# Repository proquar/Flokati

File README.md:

Flokati
=======

Flokati is a collaborative ad-hoc automation system consisting of a
(relatively) low-speed rf-part based on AVR-microcontrollers and Nordic's
NRF-ICs, an OpenWrt-based WiFi-Gateway and an Android-App as a frontend.

For convenience the Android-App and OpenWrt-package for ar71xx are provided
in binary too.

History / Motivation / Overview
===============================

The original idea was to build a system of battery-powered devices for off-
the-grid outdoor parties, it should be:
* absolutely easy to set up and to use
* fast and responsive
* used simultaneously by a few people (and be robust at that)
* relatively cheap to build

Overall it already works very well, it still has some shortcomings, but I am
working on those.

Flokati-Parts
-------------

**Devices**

*	Currently there are only some spotlights and a mirror ball motor that I
	built around the Atmega88 and NRF24L01+.
	Devices have a unique 64bit address and can have multiple controllable
	elements (e.g. brightness, speed).
	Devices use Nordic's proprietary 2.4GHz NRF-technology (which was chosen
	because it is really cheap, much cheaper than e.g. 802.15.4).

**Gateway**

*	There needs to be a bridge between the IP-world and the proprietary
	rf-world. Here it is an OpenWrt-based WiFi access point (a battery powered
	TP-Link MR11U in my case) that also acts as a DCHP-server and hosts the
	device database.

**Frontend**

*	At the moment there's only the Android-App, which discovers new devices,
	requests device metadata from the device database and allows low-level
	control of discovered devices.

Architecture
------------

On the IP-side Flokati makes heavy use of IP-multicast. The bridge and the
Android devices all join a multicast group, and changes on one Android device
are immediately visible on the others. All actions on either side (NRF and IP)
are as fast as possible broadcast to the other side.

Controllable devices broadcast notify-messages with their ID and current
settings regularly, which are received by the frontend. The frontend then looks
up metadata (like name and controllable sinks) for that device from a database
which is also distributed in a multicast group. (Though the database currently
runs on the OpenWrt gateway and is not yet distributed)

So it is also possible to have controllable devices on the IP-side, so there
are currently no implementations for this. I will also add a mechanism for
remote configuration of some devices in the near future.

Directories
===========

**/avr**

*	These are some small devices I have built, there's a spotlight, which is
	able to PWM-dim or strobe a led. A mirror ball motor with controllable
	speed and direction. And the serial<->NRF gateway that is attached to the
	OpenWrt router.
	I will add hardware schematics and board layouts later.

**/Flokati-android**

*	This is the Android App as an Eclipse project. It's tiny and without any
	additional libraries. 

**/json-db**

*	Device metadata currently used by the database server on the OpenWrt
	router. Temporary solution. Should be put into /etc/flokati/db.

**/linux/flokati**

*	This is the OpenWrt package, consisting of two server-executables (bridge
	and database) and an init-script. The bridge can indicate it's status with
	a LED, that can be configured in the init-script.

**/flokati/python**

*	A few python tools, that I used during development. They do the same as the
	C-servers for OpenWrt.

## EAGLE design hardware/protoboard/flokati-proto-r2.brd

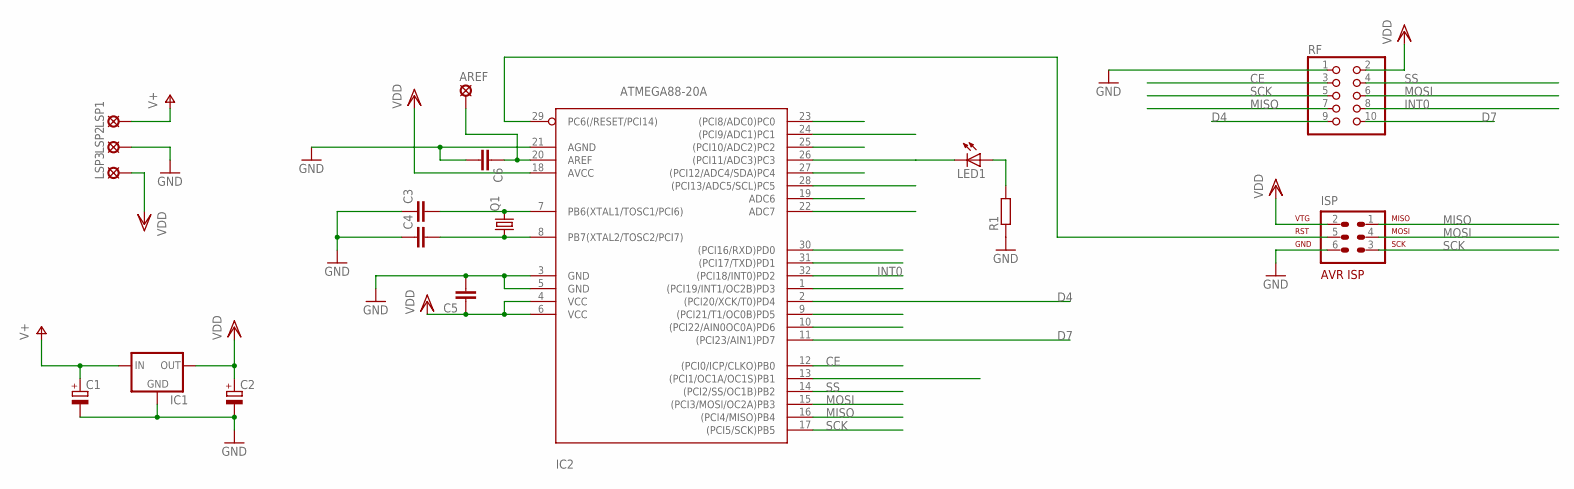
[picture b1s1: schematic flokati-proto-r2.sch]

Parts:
AREF: LSP10
C1, C2: CPOL-EUE2-4; E2-4
C3, C4, C5, C6: C-EUC0805K; C0805K
IC1: 78XXS
IC2: ATMEGA88-20A; TQFP32-08
ISP: AVR-ISP-6
LED1: LEDCHIP-LED0805; CHIP-LED0805
LSP1, LSP2, LSP3: LSP11
Q1: CRYSTALHC49U70; HC49U70
R1: R-EU_M0805; M0805
RF: PINHD-2X5; 2X05

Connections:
CE: IC2.12 ((PCI0/ICP/CLKO)PB0), RF.3
D4: IC2.2 ((PCI20/XCK/T0)PD4), RF.9
D7: IC2.11 ((PCI23/AIN1)PD7), RF.10
GND: C1.-, C2.-, C3.1, C4.1, C5.2, C6.2, IC1.GND, IC2.3 (GND), IC2.5 (GND), IC2.21 (AGND), ISP.6, LSP2.MP, R1.1, RF.1
INT0: IC2.32 ((PCI18/INT0)PD2), RF.8
MISO: IC2.16 ((PCI4/MISO)PB4), ISP.1, RF.7
MOSI: IC2.15 ((PCI3/MOSI/OC2A)PB3), ISP.4, RF.6
unnamed: C3.2, IC2.7 (PB6(XTAL1/TOSC1/PCI6)), Q1.2
unnamed: C4.2, IC2.8 (PB7(XTAL2/TOSC2/PCI7)), Q1.1
unnamed: AREF.MP, C6.1, IC2.20 (AREF)
unnamed: IC2.29 (PC6(/RESET/PCI14)), ISP.5
unnamed: IC2.26 ((PCI11/ADC3)PC3), LED1.C
unnamed: LED1.A, R1.2
SCK: IC2.17 ((PCI5/SCK)PB5), ISP.3, RF.5
SS: IC2.14 ((PCI2/SS/OC1B)PB2), RF.4
V+: C1.+, IC1.IN, LSP1.MP
VDD: C2.+, C5.1, IC1.OUT, IC2.4 (VCC), IC2.6 (VCC), IC2.18 (AVCC), ISP.2, LSP3.MP, RF.2

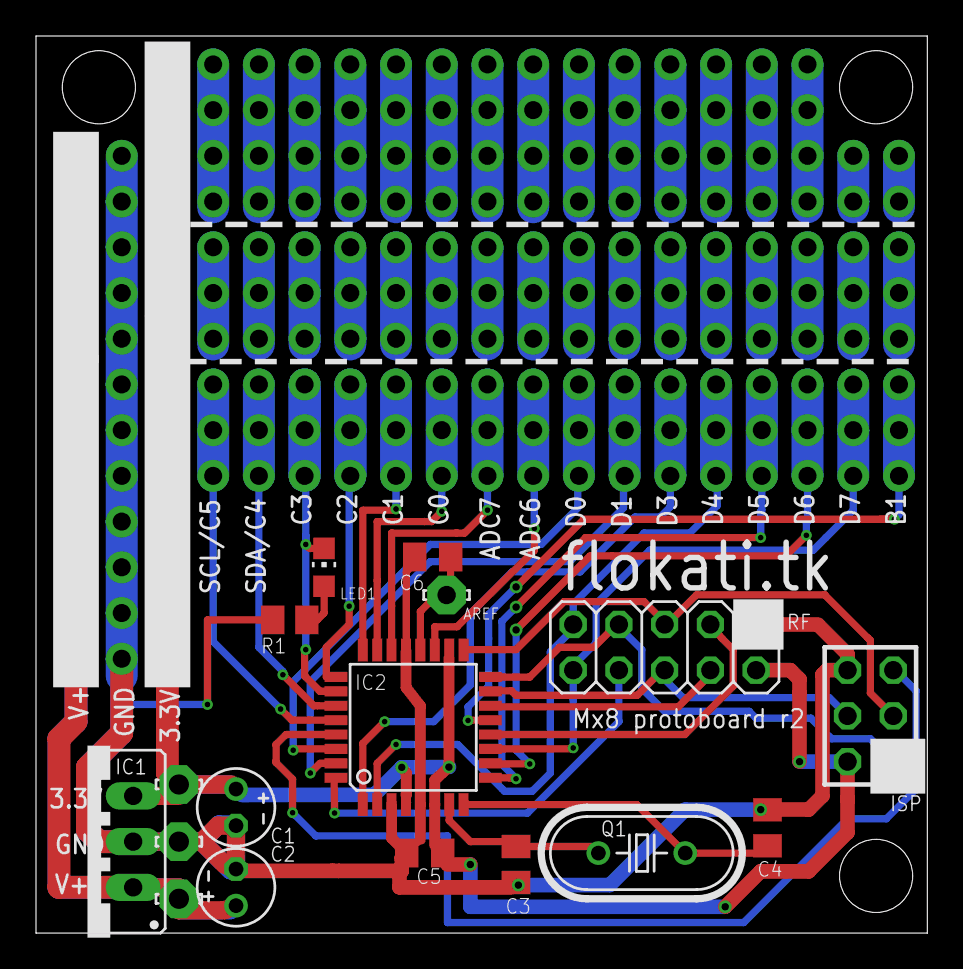
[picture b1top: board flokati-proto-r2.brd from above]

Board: 2 copper layers, 49.5 x 49.8 mm, 17 parts (0 on the bottom side), 17 nets.

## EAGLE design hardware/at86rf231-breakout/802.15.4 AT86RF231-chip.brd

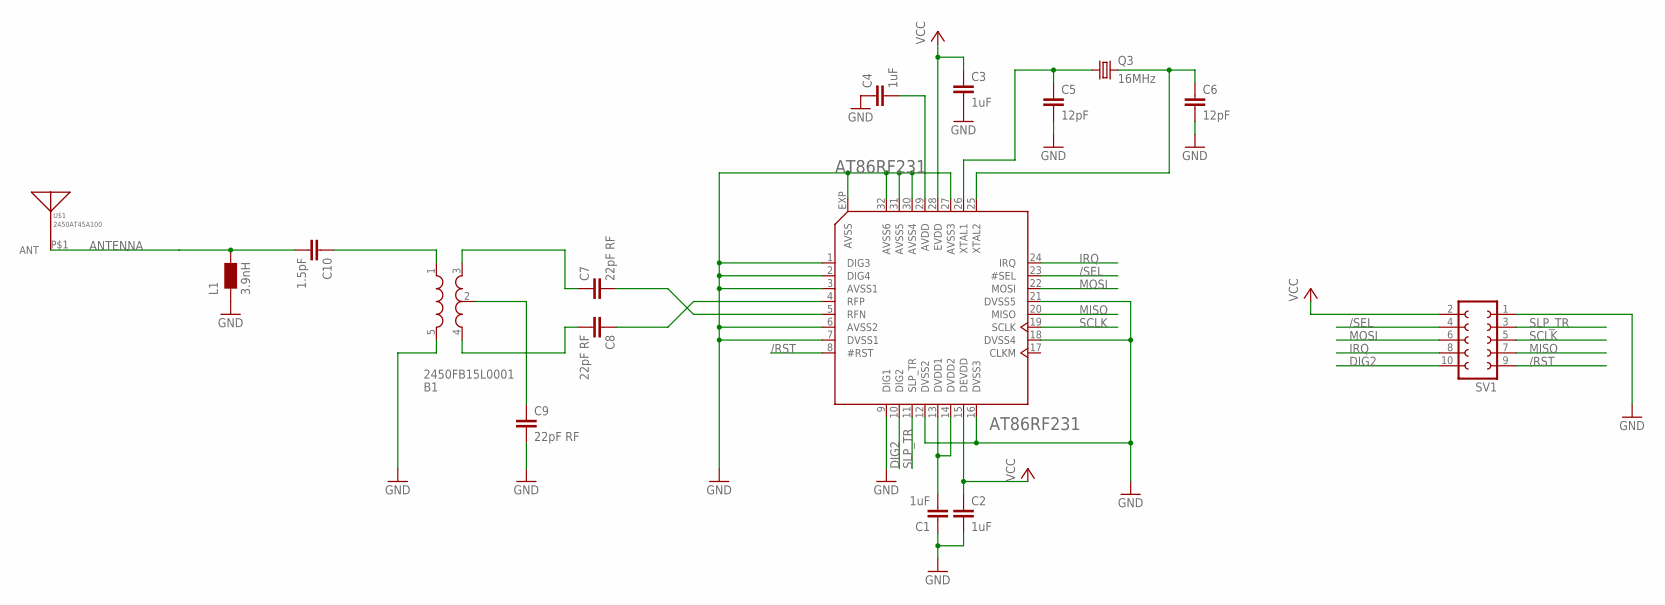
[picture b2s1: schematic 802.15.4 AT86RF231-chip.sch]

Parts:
AT86RF231: AT86RF231; QFN32
B1: 2450FB15L0001; BALUN
C1, C2, C3, C4: 1uF; C0402K
C5, C6: 12pF; C0402K
C7, C8, C9: 22pF RF; C0402K
C10: 1.5pF; C0402K
L1: 3.9nH; 0402
Q3: 16MHz; CTS406
SV1: FE05-2
U$1: 2450AT45A100

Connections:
/RST: AT86RF231.8 (#RST), SV1.9
/SEL: AT86RF231.23 (#SEL), SV1.4
ANTENNA: C10.2, L1.2, U$1.P$1
AVDD: AT86RF231.29 (AVDD), C4.2
DIG2: AT86RF231.10 (DIG2), SV1.10
DVDD1: AT86RF231.13 (DVDD1), AT86RF231.14 (DVDD2), C1.2
GND: AT86RF231.1 (DIG3), AT86RF231.2 (DIG4), AT86RF231.3 (AVSS1), AT86RF231.6 (AVSS2), AT86RF231.7 (DVSS1), AT86RF231.9 (DIG1), AT86RF231.12 (DVSS2), AT86RF231.16 (DVSS3), AT86RF231.18 (DVSS4), AT86RF231.21 (DVSS5), AT86RF231.27 (AVSS3), AT86RF231.30 (AVSS4), AT86RF231.31 (AVSS5), AT86RF231.32 (AVSS6), AT86RF231.EXP (AVSS), B1.5 (GND), C1.1, C2.2, C3.2, C4.1, C5.2, C6.2, C9.2, L1.1, SV1.1
IRQ: AT86RF231.24 (IRQ), SV1.8
MISO: AT86RF231.20 (MISO), SV1.7
MOSI: AT86RF231.22 (MOSI), SV1.6
unnamed: AT86RF231.26 (XTAL1), C5.1, Q3.1
unnamed: AT86RF231.25 (XTAL2), C6.1, Q3.3 (2)
unnamed: AT86RF231.4 (RFP), C8.1
unnamed: AT86RF231.5 (RFN), C7.2
unnamed: B1.3 (OUT1), C7.1
unnamed: B1.4 (OUT2), C8.2
unnamed: B1.2 (GND), C9.1
unnamed: B1.1 (IN), C10.1
SCLK: AT86RF231.19 (SCLK), SV1.5
SLP_TR: AT86RF231.11 (SLP_TR), SV1.3
VCC: AT86RF231.15 (DEVDD), AT86RF231.28 (EVDD), C2.1, C3.1, SV1.2

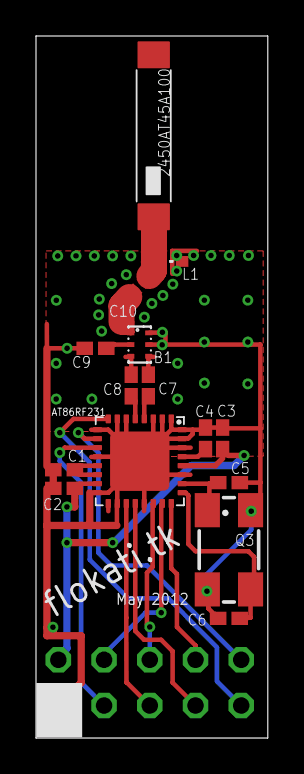
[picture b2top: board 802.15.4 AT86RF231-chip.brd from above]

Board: 2 copper layers, 12.9 x 39.0 mm, 16 parts (1 on the bottom side), 21 nets.

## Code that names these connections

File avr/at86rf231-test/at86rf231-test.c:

#include <avr/io.h>
#include <avr/interrupt.h>
#include <stdlib.h>
#include <util/delay.h>
#include "spi.h"
#include "common.h"
#include "at86rf230_registermap.h"


void uartInit(uint8_t baudrate) {
	//enable transmitter+receiver, 8 databits
	UCSR0B = (1<<TXEN0)|(1<<RXEN0);
	
	//asynchronous, no parity, 1 stopbit, 8 databits
	UCSR0C = (1<<UCSZ01)|(1<<UCSZ00);

	UBRR0H = 0;
	UBRR0L = baudrate;
}

void uartSend(const char *data) {
	uint16_t i=0;
	while (data[i]!=0) {
		UDR0=data[i];
		while(!(UCSR0A&(1<<UDRE0)));
		i++;
	}
}

int main(void) {
	STATUS_INIT();
	SEL_HIGH();
	uartInit(51);
	
	DDRB = (1<<0)|(1<<2)|(1<<3)|(1<<5); //SLP_TR, SEL, MOSI, SCK
	DDRD |= (1<<4); //reset high
	
	//spi init
	SPCR = (1<<SPE)|(1<<MSTR);
	SPSR = (1<<SPI2X);
	
	// at86rf231 init
	RES_LOW();
	SLPTR_LOW();
	_delay_ms(6);
	RES_HIGH();
	
	uint8_t allPassed=1;
	
	
	uartSend("Self-test starting.\r\n");
	
	
	uartSend("Setting new state TRX_OFF...    ");
	writeSPI_register(RG_TRX_STATE, CMD_TRX_OFF);
	
	while ( (readSPI_register(RG_TRX_STATUS)&0x1f) != TRX_OFF) ;
	uartSend("OK\r\n");
	// SPI communication works, SEL, SCLK, MOSI and MISO pins tested.
	
	
	uartSend("Testing SLP_TR pin...           ");
	writeSPI_register(RG_TRX_STATE, CMD_RX_ON);
	while ( (readSPI_register(RG_TRX_STATUS)&0x1f) != RX_ON) ;
	SLPTR_HIGH(); // state should transition to RX_ON_NOCLK
	while ( (readSPI_register(RG_TRX_STATUS)&0x1f) != RX_ON_NOCLK) ;
	SLPTR_LOW();
	while ( (readSPI_register(RG_TRX_STATUS)&0x1f) != RX_ON) ;
	uartSend("OK\r\n");
	
	
	// we were in RX_ON state, Reset should bring us back into TRX_OFF
	uartSend("Testing RESET pin...            ");
	RES_LOW();
	_delay_ms(6);
	RES_HIGH();
	while ( (readSPI_register(RG_TRX_STATUS)&0x1f) != TRX_OFF) ;
	uartSend("OK\r\n");
	
	
	uartSend("Enabling relevant interrupts... ");
	writeSPI_register(RG_IRQ_MASK, (1<<2)|(1<<3)); //RX_START,TRX_END
	
	while ( (readSPI_register(RG_IRQ_MASK))!= ((1<<2)|(1<<3))) ;
	uartSend("OK\r\n");
	
	
	uartSend("Enabling DIG2 pin...            ");
	writeSPI_register(RG_TRX_CTRL_1, 0x60);
	
	while ( (readSPI_register(RG_TRX_CTRL_1))!= 0x60) ;
	uartSend("OK\r\n");
	
	
	// as described in datasheet 10.2
	uartSend("Sending dummy frame...          ");
	writeSPI_register(RG_TRX_STATE, CMD_PLL_ON); //sending mode
	while ( (readSPI_register(RG_TRX_STATUS)&0x1f) != PLL_ON) ;
	writeFrame((uint8_t *)"FOOBAR", 6);
	SLPTR_HIGH(); //start sending, same as setting TRX_START mode
	_delay_ms(1);
	SLPTR_LOW();
	while(IRQ_PIN()==0); //wait for TRX_END on interrupt pin
	if (readSPI_register(RG_IRQ_STATUS)&(1<<3)) { // TRX_END should now be set
		while (IRQ_PIN()!=0) ; //IRQ pin should clear after reading IRQ_STATUS
		writeSPI_register(RG_TRX_STATE, CMD_RX_ON);
		uartSend("OK\r\n");
		uartSend("IRQ pin working...              OK\r\n");
	} else {
		writeSPI_register(RG_TRX_STATE, CMD_RX_ON);
		uartSend("ERROR\r\n");
		allPassed=0;
	}
	
	while ( (readSPI_register(RG_TRX_STATUS)&0x1f) != RX_ON) ;
	
	uartSend("Listening for frame...          ");
	while (DIG2_PIN()==0); // test DIG2 pin, should be issued the same time as RX_START
	uint8_t interrupts = readSPI_register(RG_IRQ_STATUS);
	if (interrupts&(1<<2)) { // RX_START
		if (!(interrupts&(1<<3))) { // wait for TRX_END
			while (IRQ_PIN()==0) ;
			while (!(readSPI_register(RG_IRQ_STATUS)&(1<<3))) ;
		}
		uartSend("OK\r\n");
		uartSend("DIG2 pin working...             OK\r\n");
	} else {
		uartSend("ERROR\r\n");
		allPassed=0;
	}
	
	uartSend("\r\n##################################\r\n");
	if (allPassed) {
		STATUS_ON();
		uartSend("########## PASSED ################\r\n");
	}
	else
		uartSend("######## NOT PASSED ##############\r\n");
	uartSend("##################################\r\n");
	
	_delay_ms(1000);
	uartSend("\r\n\r\n");
	
	uint8_t frame[129];
	while(1) {
		uint8_t interrupts = readSPI_register(RG_IRQ_STATUS);
		if (interrupts&(1<<3)) {
			STATUS_OFF();
			uint8_t len = readFrame(frame);
			uartSend("LQI: ");
			char value[4];
			value[3]=0;
			uartSend(utoa(frame[len],value,10));
			uartSend("\r\n");
			
			_delay_ms(10);
			
			//reply
			while ( (readSPI_register(RG_TRX_STATUS)&0x1f) != RX_ON) ;
			writeSPI_register(RG_TRX_STATE, CMD_PLL_ON);
			while ( (readSPI_register(RG_TRX_STATUS)&0x1f) != PLL_ON) ;
			writeFrame((uint8_t *)"FOOBAR", 6);
			writeSPI_register(RG_TRX_STATE, CMD_TX_START);
			while ( (readSPI_register(RG_TRX_STATUS)&0x1f) != PLL_ON) ;
			
			writeSPI_register(RG_TRX_STATE, CMD_RX_ON);
			while ( (readSPI_register(RG_TRX_STATUS)&0x1f) != RX_ON) ;
			
			
			_delay_ms(50);
			STATUS_ON();
		}
	}
	
	return 0;
}

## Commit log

2012-04-27 Created gh-pages branch via GitHub
2012-04-27 Fixed markup
2012-04-27 Fixed markup (again)
2012-04-27 cozy
2012-04-30 Init script now adds route to multicast ip range.
2012-04-30 Fixed syntax error (comma where none should be)
2012-05-05 Changed group address, message format on UDP now contains last byte of group address.
2012-10-20 Added AT86RF231 Testprogram, protoboard rev. 2 design files and AT86RF231 breakout board (chip antenna version) design files. All tested and working.
2013-02-01 Increased buffer size for incoming UDP packets.
2013-05-03 Fixed bug in Reception of UDP packets and conversion to JSON-object in Android App.
2013-05-11 Fixed a bug in the spotlight when switching from dimmed to strobe-mode New feature in spotlight: inverted or normal mode selectable with macro New stand-alone strobe controller for external flashes

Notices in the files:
parts and their libraries:
SparkFun: Licensing: CC v3.0 Share-Alike You are welcome to use this library for commercial purposes.
wuerth-elektronik: Copyright: Würth Elektronik eiSos
